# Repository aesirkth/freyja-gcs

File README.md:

freyja ground control station. talks with launchpad controller surtr over lora through brage and to fjaelar over brage.

## goals
- pcb should be able to run standalone from raspberry in case of raspberry malfunction
- every part from lcsc so that pcb can be assembled by jlcpcb. only select parts that have lot in stock. 
- 4-layer pcb. mainly for usb signal integrity

## tools
kicad + the plugin [impartGUI](https://github.com/Steffen-W/Import-LIB-KiCad-Plugin). impartGUI makes it really easy to get symbols and footprints downloaded directly from lcsc.

## TODO PCB
- [x] ESD/TVS diodes on every connecter and button
- Layout
- [x] configure stackup according to jlcpcb specs
- [x] usb 90 ohm diff-z
- [x] valve toggle switches
- [x] arm keyrings
- [x] 7-segment for redundancy operation without rpi
- leds:
  - [x] armed
  - [x] led for every valve toggle. should only be activated if surtr confirms position. blink if state is unknown
  - [x] connection status with surtr
  - [x] connection status with fjaelar
  - [x] fault
- [x] battery charging circuit
  - [x] undervoltage lockout
- [x] raspberry pi power
- [x] 2 can ports
  - [x] one for brage 
  - [x] one for connecting directly to launchpad
- [x] short circuit protection
- [x] fan connector
- [x] battery ntc work up to 70deg
- [x] led backlight driver
- [x] correct mounting holes
  - [x] dnp on resistors
- [ ] export 3d model and place raspberry to check fitment
- [x] silkscreen
  - [X] designators
  - [x] pinout
  - [x] name
  - [x] aesir
  - [x] connection
  - [x] battery polarity

## Components selection 
- 2 LiPo cells in series. (7.2V = 3.7 + 3.7V)
- Use DC-DC buck to step down the voltage to power RPi (min 4A continious current).
- We have to find a charging circuit for the 7.2V battries.
- Flip the toggle switch and hit send button to send command to sutur (this has to be done in the software).
- Therefore we will have 7 switches (6 toggle + 1 send)(in pull-up config).

### Part ID from LCSC
- C100042 - Capacitor
- C1788487 - Toggle switch
- C268254 - Push switch
- C965807 - Blue LED
- C965804 - Green LED
- C965799 - Red LED
- C95299 - Buzzer
- C42435361 - push button
- C18221474 - DC-DC booster
- C98220 - 10k ohm resistor

## To order
- [ ] 10-pin jst ph
- [ ] pcb

## SOFTWARE

We need two code bases. One Zephyr application that runs on the GCS PCB (PCB APP). And one Javascript and React + Python Raspberry Pi app (RPI APP) for displaying and managing the telemetry data. 

### PCB APP

Specs:
- Zephyr
- Talks with rocket and pad control through brage over CAN FD
- USB CDC to send data to RPI. Choose appropriate serialization format. 
- Sends valve toggle position only when send button has been pressed. 
- Shows status of valve on led.  

### RPI APP

Specs:
- Data to show:
  - Analog
    - With plot:
      - Altitude
      - Thrust. From loadcell. 
      - Orientation (from IMU)
      - Airbrake percantage
    - Without plot (only value):
      - Speed
      - Battery voltage
      - Countdown
      - Tank temperature. 6 ones spread over the tank.
      - Injector temperature
      - Post-combustion chamber temperature. 2 ones. 
      - Nozzle temperature. 2 ones.
      - Pressure at injector. 3 ones. 
    - Misc.
      - (GPS map if time over)
  - Discrete/bool:
    - Valve status (closed/open/unknown). 5 or 6 valves. 
    - Disarmed/armed
    - Ready/launched
    - Connection status with launch pad Surtr (down/up)
    - Connection status with rocket Fjalar (down/up)
    - Tank full float switch. (full/not full)
    - Main valve actuator (closed/open/unknown)
    - Abort valve actuator (closed/open/unknown)
    - CO2 activated [yes/no]
    - Parachute line cutters. 2 ones.
    - umbilical disconnect
    - tank bleed valve
- Gets binary data stream from GCS PCB. Hugo will help with protocol
  pack/unpack. [See wiki comparison of serialization formats](https://en.wikipedia.org/wiki/Comparison_of_data-serialization_formats). Maybe choose Protobuf or similar?
- Database to store all data

## venv
to activate python venv. have uv installed and execute
```
uv venv --system-site-packages
uv pip install -r pyproject.toml
```

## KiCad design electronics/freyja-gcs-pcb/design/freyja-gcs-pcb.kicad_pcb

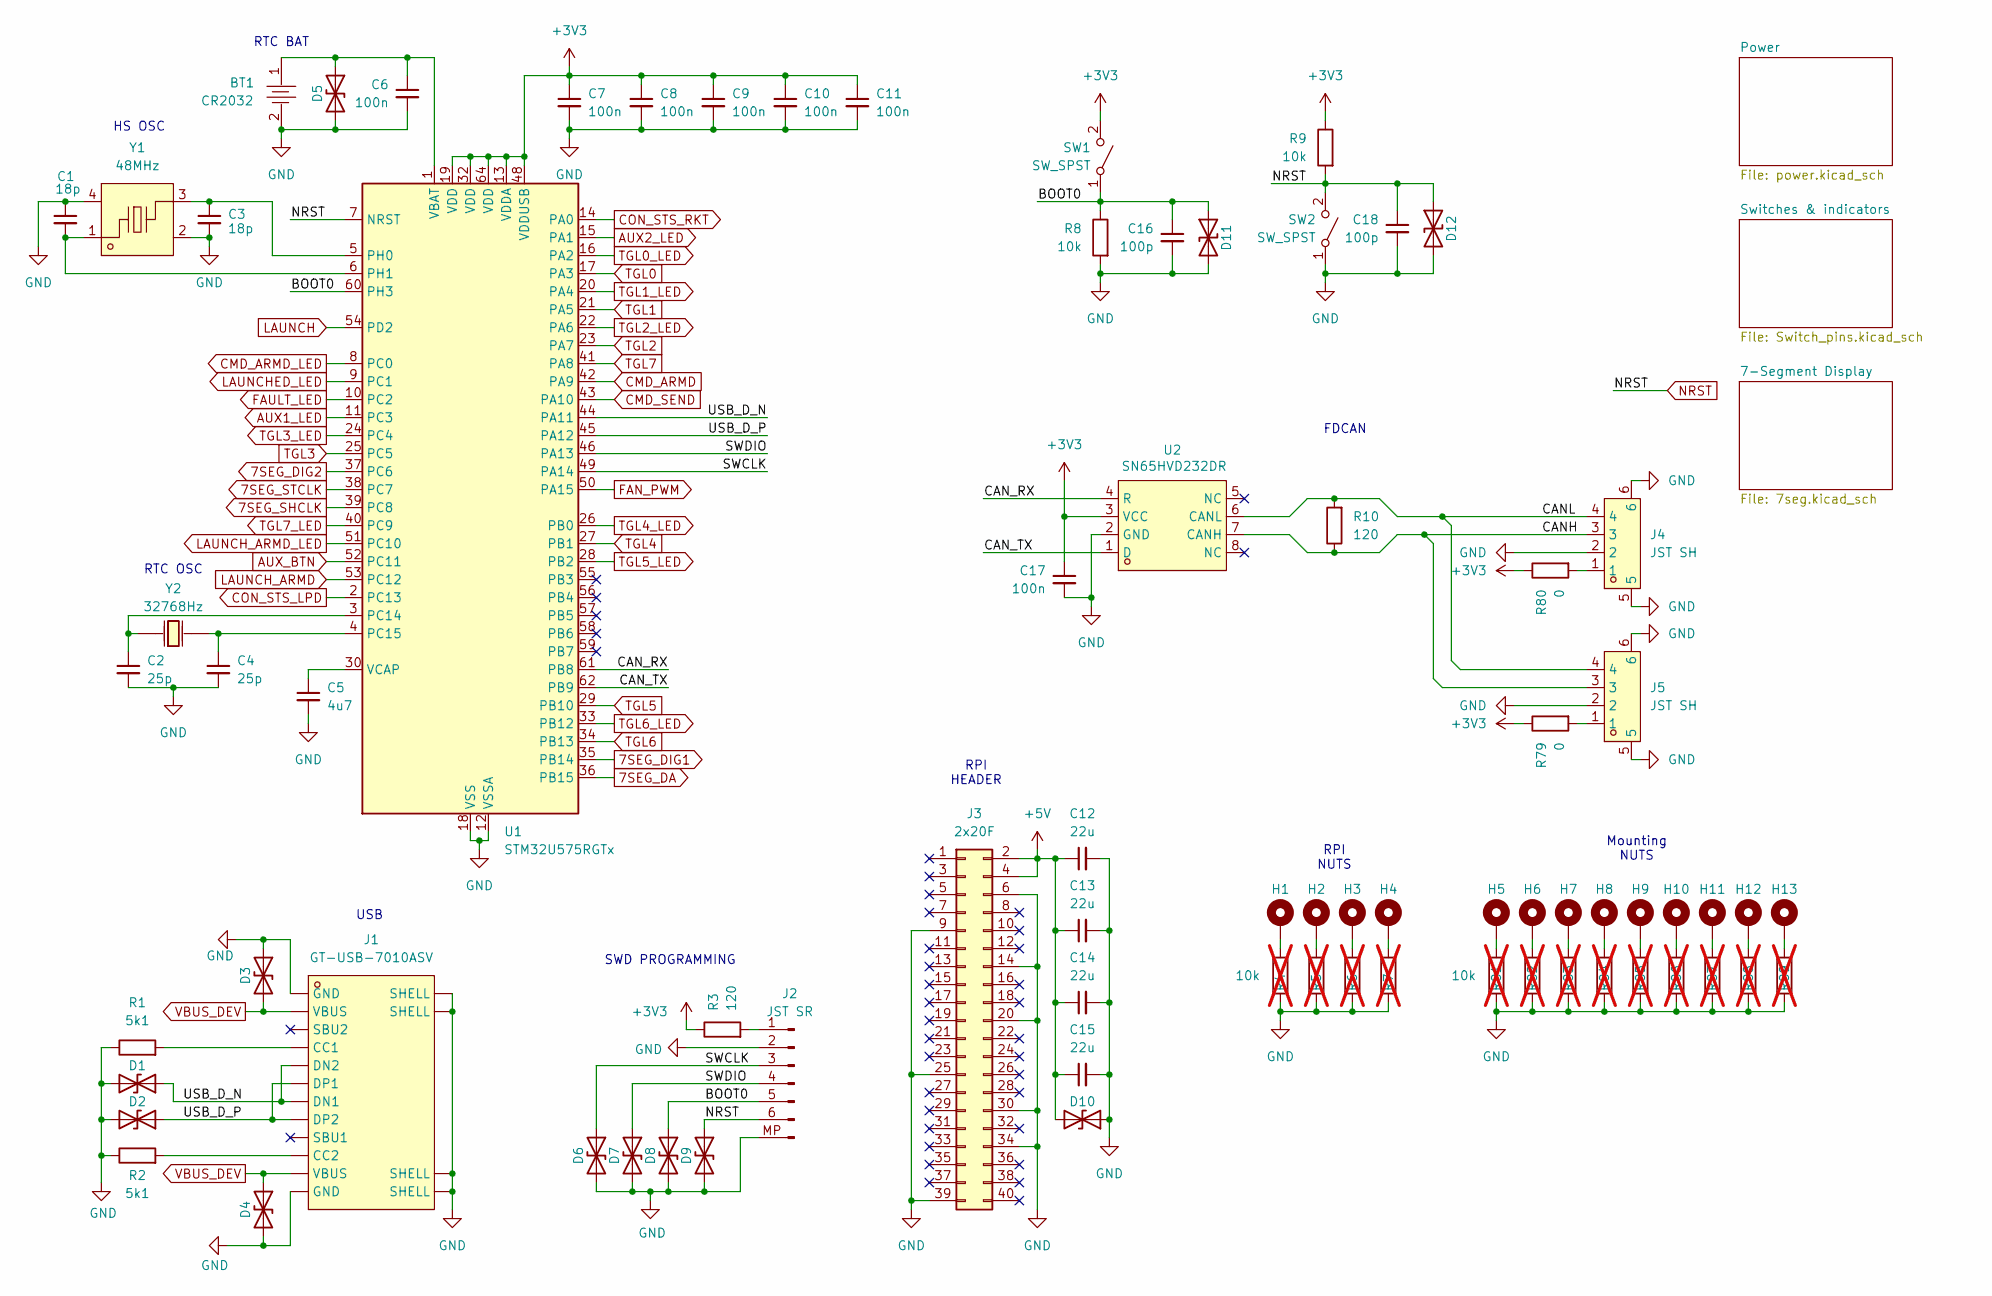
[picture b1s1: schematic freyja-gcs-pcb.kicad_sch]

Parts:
BT1: CR2032; BAT-TH_BS-2-1; LCSC Part C70376
C1, C3: 18p; C_0603_1608Metric; LCSC Part C5137620
C2, C4: 25p; C_0603_1608Metric; LCSC Part C282067
C5: 4u7; C_0603_1608Metric; LCSC Part C19666
C6, C7, C8, C9, C10, C11, C17: 100n; C_0603_1608Metric; LCSC Part C2762593
C12, C13, C14, C15: 22u; C1210; LCSC Part C100086
C16, C18: 100p; C_0603_1608Metric; LCSC Part C14665
D1, D2, D3, D4, D5, D6, D7, D8, D9, D10, D11, D12: 0603ESDA-05N; D_0603_1608Metric_Pad1.05x0.95mm_HandSolder; LCSC Part C316054
H1, H2, H3, H4: M2.5 12mm; SMTSO25120; LCSC Part C30182754
H5, H6, H7, H8, H9, H10, H11, H12, H13: M2.5 12mm; SMTSO25100; LCSC Part C2916330
J1: GT-USB-7010ASV; USB-C-SMD_G-SWITCH_GT-USB-7010ASV; LCSC Part C2988369
J2: JST SR; JST_SH_SM06B-SRSS-TB_1x06-1MP_P1.00mm_Horizontal; LCSC Part C2764185
J3: 2x20F; PinSocket_2x20_P2.54mm_Vertical; LCSC Part C2977589
J4, J5: JST SH; CONN-SMD_AFC10-S04QCA-00; LCSC Part C2764183
R1, R2: 5k1; R_0603_1608Metric; LCSC Part C23186
R3, R10: 120; R_0603_1608Metric; LCSC Part C22787
R4, R5, R6, R7, R81, R82, R83, R84, R85, R86, R87, R88, R89: 10k; R_0603_1608Metric; LCSC Part C98220; not fitted
R8, R9: 10k; R_0603_1608Metric; LCSC Part C98220
R79, R80: 0; R_0603_1608Metric; LCSC Part C2906974
SW1, SW2: SW_SPST; SW_SPST_PTS647_Sx38; LCSC Part C2689502
U1: STM32U575RGTx; LQFP-64_10x10mm_P0.5mm; LCSC Part C5270980
U2: SN65HVD232DR; SOIC-8_L5.0-W4.0-P1.27-LS6.0-BL; LCSC Part C30530
Y1: 48MHz; CRYSTAL-SMD_4P-L2.0-W1.6-BL_HUAXIN_CN4; LCSC Part C2933019
Y2: 32768Hz; OSC-TH_BD1.9-P0.70; LCSC Part C403947

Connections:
7SEG_DA: U1.36 (PB15); also elsewhere on the board
7SEG_DIG1: U1.35 (PB14); also elsewhere on the board
7SEG_DIG2: U1.37 (PC6); also elsewhere on the board
7SEG_SHCLK: U1.39 (PC8); also elsewhere on the board
7SEG_STCLK: U1.38 (PC7); also elsewhere on the board
+3V3: C7.1, C8.1, C9.1, C10.1, C11.1, C17.1, R3.1, R9.1, R79.1, R80.1, SW1.2 (B), U1.13 (VDDA), U1.19 (VDD), U1.32 (VDD), U1.48 (VDDUSB), U1.64 (VDD), U2.3 (VCC); also elsewhere on the board
+5V: C12.1, C13.1, C14.1, C15.1, D10.2 (A2), J3.2, J3.4; also elsewhere on the board
/BOOT0: C16.1, D8.1 (A1), D11.1 (A1), J2.5, R8.1, SW1.1 (A), U1.60 (PH3)
/CANH: J4.3, J5.3, R10.1, U2.7 (CANH)
/CANL: J4.4, J5.4, R10.2, U2.6 (CANL)
/CAN_RX: U1.61 (PB8), U2.4 (R)
/CAN_TX: U1.62 (PB9), U2.1 (D)
/SWCLK: D6.1 (A1), J2.3, U1.49 (PA14)
/SWDIO: D7.1 (A1), J2.4, U1.46 (PA13)
/USB_D_N: D1.1 (A1), J1.A7 (DN1), J1.B7 (DN2), U1.44 (PA11)
/USB_D_P: D2.1 (A1), J1.A6 (DP1), J1.B6 (DP2), U1.45 (PA12)
AUX1_LED: U1.11 (PC3); also elsewhere on the board
AUX2_LED: U1.15 (PA1); also elsewhere on the board
AUX_BTN: U1.52 (PC11); also elsewhere on the board
CMD_ARMD: U1.42 (PA9); also elsewhere on the board
CMD_ARMD_LED: U1.8 (PC0); also elsewhere on the board
CMD_SEND: U1.43 (PA10); also elsewhere on the board
CON_STS_LPD: U1.2 (PC13); also elsewhere on the board
CON_STS_RKT: U1.14 (PA0); also elsewhere on the board
FAN_PWM: U1.50 (PA15); also elsewhere on the board
FAULT_LED: U1.10 (PC2); also elsewhere on the board
GND: BT1.2, C1.1, C2.2, C3.2, C4.2, C5.2, C6.2, C7.2, C8.2, C9.2, C10.2, C11.2, C12.2, C13.2, C14.2, C15.2, C16.2, C17.2, C18.2, D1.2 (A2), D2.2 (A2), D3.1 (A1), D4.2 (A2), D5.2 (A2), D6.2 (A2), D7.2 (A2), D8.2 (A2), D9.2 (A2), D10.1 (A1), D11.2 (A2), D12.2 (A2), J1.1 (SHELL), J1.2 (SHELL), J1.3 (SHELL), J1.4 (SHELL), J1.A1B12 (GND), J1.B1A12 (GND), J2.2, J2.MP, J3.6, J3.9, J3.14, J3.20, J3.25, J3.30, J3.34, J3.39, J4.2, J4.5, J4.6, J5.2, J5.5, J5.6, R1.1, R2.1, R4.2, R5.2, R6.2, R7.2, R8.2, R81.2, R82.2, R83.2, R84.2, R85.2, R86.2, R87.2, R88.2, R89.2, SW2.1 (A), U1.12 (VSSA), U1.18 (VSS), U1.31 (VSS), U1.47 (VSS), U1.63 (VSS), U2.2 (GND), Y1.2 (GND), Y1.4 (GND); also elsewhere on the board
LAUNCH: U1.54 (PD2); also elsewhere on the board
LAUNCHED_LED: U1.9 (PC1); also elsewhere on the board
LAUNCH_ARMD: U1.53 (PC12); also elsewhere on the board
LAUNCH_ARMD_LED: U1.51 (PC10); also elsewhere on the board
NRST: C18.1, D9.1 (A1), D12.1 (A1), J2.6, R9.2, SW2.2 (B), U1.7 (NRST); also elsewhere on the board
unnamed: BT1.1, C6.1, D5.1 (A1), U1.1 (VBAT)
unnamed: H1.1, R4.1
unnamed: H2.1, R5.1
unnamed: H3.1, R6.1
unnamed: H4.1, R7.1
unnamed: H5.1, R81.1
unnamed: H6.1, R82.1
unnamed: H7.1, R83.1
unnamed: H8.1, R84.1
unnamed: H9.1, R85.1
unnamed: H10.1, R86.1
unnamed: H11.1, R87.1
unnamed: H12.1, R88.1
unnamed: H13.1, R89.1
unnamed: J1.A5 (CC1), R1.2
unnamed: J1.B5 (CC2), R2.2
unnamed: J2.1, R3.2
unnamed: J4.1, R80.2
unnamed: J5.1, R79.2
unnamed: C2.1, U1.3 (PC14), Y2.1 (OSC1)
unnamed: C4.1, U1.4 (PC15), Y2.2 (OSC2)
unnamed: C3.1, U1.5 (PH0), Y1.3
unnamed: C1.2, U1.6 (PH1), Y1.1
unnamed: C5.1, U1.30 (VCAP)
TGL0: U1.17 (PA3); also elsewhere on the board
TGL0_LED: U1.16 (PA2); also elsewhere on the board
TGL1: U1.21 (PA5); also elsewhere on the board
TGL1_LED: U1.20 (PA4); also elsewhere on the board
TGL2: U1.23 (PA7); also elsewhere on the board
TGL2_LED: U1.22 (PA6); also elsewhere on the board
TGL3: U1.25 (PC5); also elsewhere on the board
TGL3_LED: U1.24 (PC4); also elsewhere on the board
TGL4: U1.27 (PB1); also elsewhere on the board
TGL4_LED: U1.26 (PB0); also elsewhere on the board
TGL5: U1.29 (PB10); also elsewhere on the board
TGL5_LED: U1.28 (PB2); also elsewhere on the board
TGL6: U1.34 (PB13); also elsewhere on the board
TGL6_LED: U1.33 (PB12); also elsewhere on the board
TGL7: U1.41 (PA8); also elsewhere on the board
TGL7_LED: U1.40 (PC9); also elsewhere on the board
VBUS_DEV: D3.2 (A2), D4.1 (A1), J1.A4B9 (VBUS), J1.B4A9 (VBUS); also elsewhere on the board

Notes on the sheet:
HS OSC
FDCAN
RTC BAT
SWD PROGRAMMING
RPI HEADER
RTC OSC
Mounting NUTS
RPI NUTS
USB

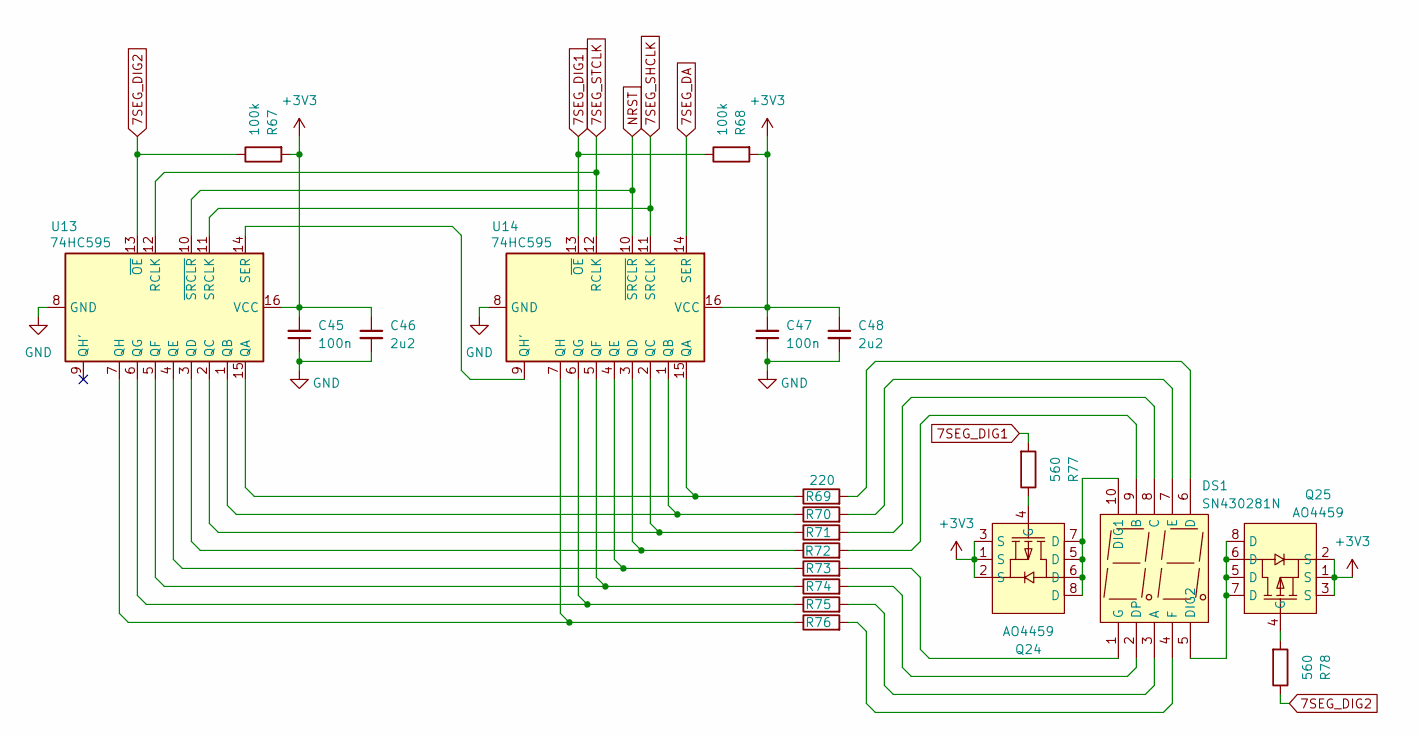
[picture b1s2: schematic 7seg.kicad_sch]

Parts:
C45, C47: 100n; C_0603_1608Metric; LCSC Part C2762593
C46, C48: 2u2; C_0603_1608Metric; LCSC Part C913904
DS1: SN430281N; LED-SEG-TH_10P-L15.0-W10.0-P2.54-S7.40-BL; LCSC Part C182258
Q24, Q25: AO4459; SOP-8_L5.0-W4.0-P1.27-LS6.2-BL; LCSC Part C49047
R67, R68: 100k; R_0603_1608Metric; LCSC Part C25803
R69, R70, R71, R72, R73, R74, R75, R76: 220; R_0603_1608Metric; LCSC Part C22962
R77, R78: 560; R_0603_1608Metric; LCSC Part C23204
U13, U14: 74HC595; SOIC-16_L9.9-W3.9-P1.27-LS6.0-BL; LCSC Part C5947

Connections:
7SEG_DA: U14.14 (SER); also elsewhere on the board
7SEG_DIG1: R68.1, R77.2, U14.13 (~OE); also elsewhere on the board
7SEG_DIG2: R67.1, R78.1, U13.13 (~OE); also elsewhere on the board
7SEG_SHCLK: U13.11 (SRCLK), U14.11 (SRCLK); also elsewhere on the board
7SEG_STCLK: U13.12 (RCLK), U14.12 (RCLK); also elsewhere on the board
+3V3: C45.2, C46.1, C47.2, C48.1, Q24.1 (S), Q24.2 (S), Q24.3 (S), Q25.1 (S), Q25.2 (S), Q25.3 (S), R67.2, R68.2, U13.16 (VCC), U14.16 (VCC); also elsewhere on the board
GND: C45.1, C46.2, C47.1, C48.2, U13.8 (GND), U14.8 (GND); also elsewhere on the board
NRST: U13.10 (~SRCLR), U14.10 (~SRCLR); also elsewhere on the board
unnamed: DS1.3 (A), R75.2
unnamed: DS1.9 (B), R72.2
unnamed: DS1.8 (C), R71.2
unnamed: DS1.6 (D), R69.2
unnamed: DS1.10 (DIG1), Q24.5 (D), Q24.6 (D), Q24.7 (D), Q24.8 (D)
unnamed: DS1.5 (DIG2), Q25.5 (D), Q25.6 (D), Q25.7 (D), Q25.8 (D)
unnamed: DS1.2 (DP), R74.2
unnamed: DS1.7 (E), R70.2
unnamed: DS1.4 (F), R76.2
unnamed: DS1.1 (G), R73.2
unnamed: Q24.4 (G), R77.1
unnamed: Q25.4 (G), R78.2
unnamed: R69.1, U13.15 (QA), U14.15 (QA)
unnamed: R70.1, U13.1 (QB), U14.1 (QB)
unnamed: R71.1, U13.2 (QC), U14.2 (QC)
unnamed: R72.1, U13.3 (QD), U14.3 (QD)
unnamed: R73.1, U13.4 (QE), U14.4 (QE)
unnamed: R74.1, U13.5 (QF), U14.5 (QF)
unnamed: R75.1, U13.6 (QG), U14.6 (QG)
unnamed: R76.1, U13.7 (QH), U14.7 (QH)
unnamed: U13.14 (SER), U14.9 (QH')

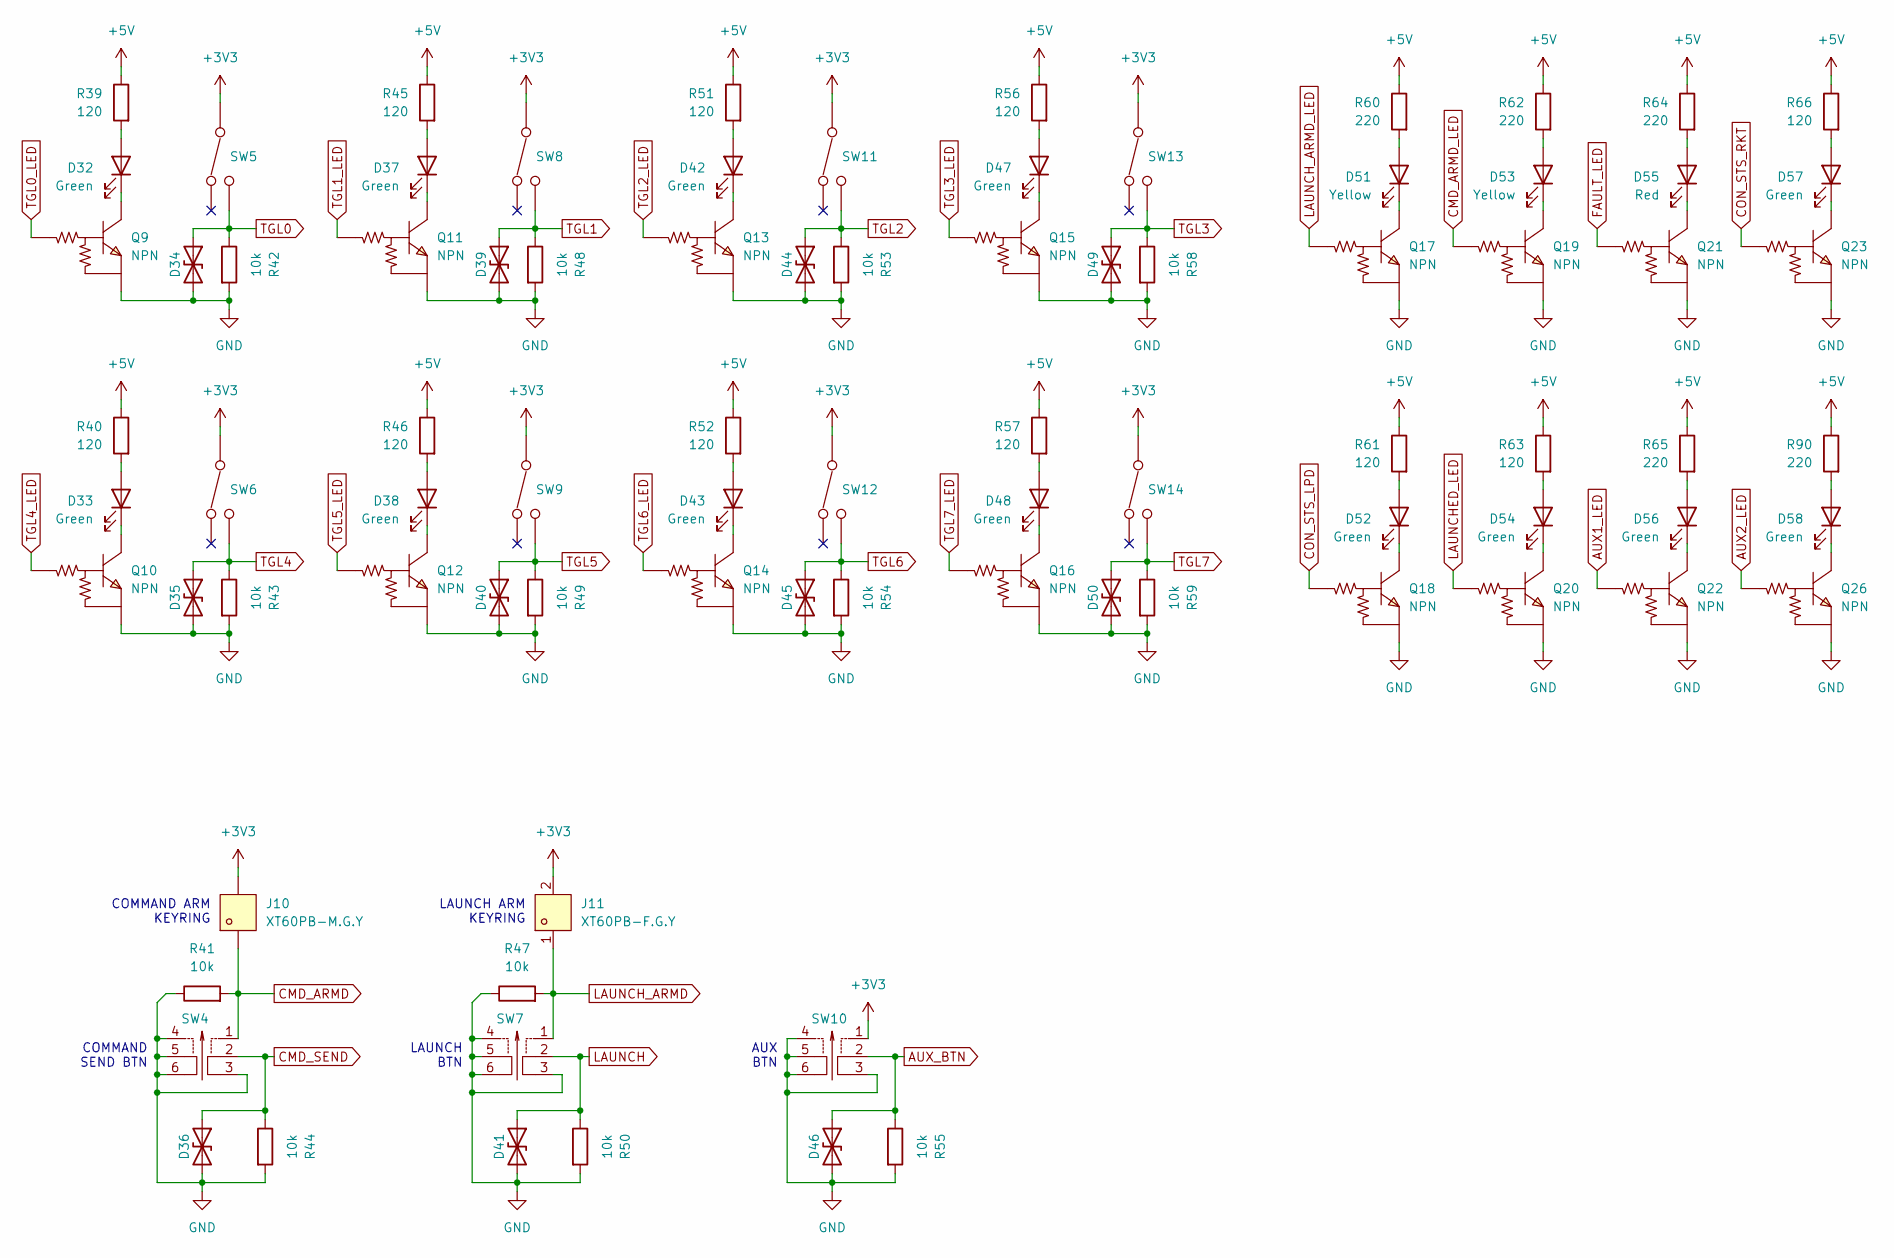
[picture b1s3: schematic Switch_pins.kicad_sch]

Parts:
D32, D33, D37, D38, D42, D43, D47, D48, D52, D54, D56, D57, D58: Green; LED-TH_BD5.9-P2.54-RD_GREEN; LCSC Part C2895548
D34, D35, D36, D39, D40, D41, D44, D45, D46, D49, D50: 0603ESDA-05N; D_0603_1608Metric_Pad1.05x0.95mm_HandSolder; LCSC Part C316054
D51, D53: Yellow; LED-TH_BD5.9-P2.54-RD_GREEN; LCSC Part C2895494
D55: Red; LED-TH_BD5.9-P2.54-RD_GREEN; LCSC Part C2895492
J10: XT60PB-M.G.Y; CONN-TH_XT60PB-M; LCSC Part C19268037
J11: XT60PB-F.G.Y; CONN-TH_XT60PB-F.G.Y; LCSC Part C19268038
Q9, Q10, Q11, Q12, Q13, Q14, Q15, Q16, Q17, Q18, Q19, Q20, Q21, Q22, Q23, Q26: NPN; SOT-416_L1.6-W0.8-P1.00-LS1.6-BR; LCSC Part C96459
R39, R40, R45, R46, R51, R52, R56, R57, R61, R63, R66: 120; R_0603_1608Metric; LCSC Part C22787
R41, R42, R43, R44, R47, R48, R49, R50, R53, R54, R55, R58, R59: 10k; R_0603_1608Metric; LCSC Part C98220
R60, R62, R64, R65, R90: 220; R_0603_1608Metric; LCSC Part C22962
SW4, SW7, SW10: PB22E09071; SW-TH_6P-L8.5-W8.5-P2.54-LS5.5; LCSC Part C194405
SW5, SW6, SW8, SW9, SW11, SW12, SW13, SW14: 2MS1T1B1M2QES; SW-TH_2MS1T1B1M2QES-5; LCSC Part C908280

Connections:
+3V3: J10.2, J11.2, SW5.2, SW6.2, SW8.2, SW9.2, SW10.1, SW11.2, SW12.2, SW13.2, SW14.2; also elsewhere on the board
+5V: R39.1, R40.1, R45.1, R46.1, R51.1, R52.1, R56.1, R57.1, R60.1, R61.1, R62.1, R63.1, R64.1, R65.1, R66.1, R90.1; also elsewhere on the board
AUX1_LED: Q22.1 (B); also elsewhere on the board
AUX2_LED: Q26.1 (B); also elsewhere on the board
AUX_BTN: D46.1 (A1), R55.1, SW10.2; also elsewhere on the board
CMD_ARMD: J10.1, R41.2, SW4.1; also elsewhere on the board
CMD_ARMD_LED: Q19.1 (B); also elsewhere on the board
CMD_SEND: D36.1 (A1), R44.1, SW4.2; also elsewhere on the board
CON_STS_LPD: Q18.1 (B); also elsewhere on the board
CON_STS_RKT: Q23.1 (B); also elsewhere on the board
FAULT_LED: Q21.1 (B); also elsewhere on the board
GND: D34.2 (A2), D35.2 (A2), D36.2 (A2), D39.2 (A2), D40.2 (A2), D41.2 (A2), D44.2 (A2), D45.2 (A2), D46.2 (A2), D49.2 (A2), D50.2 (A2), Q9.2 (E), Q10.2 (E), Q11.2 (E), Q12.2 (E), Q13.2 (E), Q14.2 (E), Q15.2 (E), Q16.2 (E), Q17.2 (E), Q18.2 (E), Q19.2 (E), Q20.2 (E), Q21.2 (E), Q22.2 (E), Q23.2 (E), Q26.2 (E), R41.1, R42.2, R43.2, R44.2, R47.1, R48.2, R49.2, R50.2, R53.2, R54.2, R55.2, R58.2, R59.2, SW4.3, SW4.4, SW4.5, SW4.6, SW7.3, SW7.4, SW7.5, SW7.6, SW10.3, SW10.4, SW10.5, SW10.6; also elsewhere on the board
LAUNCH: D41.1 (A1), R50.1, SW7.2; also elsewhere on the board
LAUNCHED_LED: Q20.1 (B); also elsewhere on the board
LAUNCH_ARMD: J11.1, R47.2, SW7.1; also elsewhere on the board
LAUNCH_ARMD_LED: Q17.1 (B); also elsewhere on the board
unnamed: D32.2 (A), R39.2
unnamed: D32.1 (K), Q9.3 (C)
unnamed: D33.2 (A), R40.2
unnamed: D33.1 (K), Q10.3 (C)
unnamed: D37.2 (A), R45.2
unnamed: D37.1 (K), Q11.3 (C)
unnamed: D38.2 (A), R46.2
unnamed: D38.1 (K), Q12.3 (C)
unnamed: D42.2 (A), R51.2
unnamed: D42.1 (K), Q13.3 (C)
unnamed: D43.2 (A), R52.2
unnamed: D43.1 (K), Q14.3 (C)
unnamed: D47.2 (A), R56.2
unnamed: D47.1 (K), Q15.3 (C)
unnamed: D48.2 (A), R57.2
unnamed: D48.1 (K), Q16.3 (C)
unnamed: D51.2 (A), R60.2
unnamed: D51.1 (K), Q17.3 (C)
unnamed: D52.2 (A), R61.2
unnamed: D52.1 (K), Q18.3 (C)
unnamed: D53.2 (A), R62.2
unnamed: D53.1 (K), Q19.3 (C)
unnamed: D54.2 (A), R63.2
unnamed: D54.1 (K), Q20.3 (C)
unnamed: D55.2 (A), R64.2
unnamed: D55.1 (K), Q21.3 (C)
unnamed: D56.2 (A), R65.2
unnamed: D56.1 (K), Q22.3 (C)
unnamed: D57.2 (A), R66.2
unnamed: D57.1 (K), Q23.3 (C)
unnamed: D58.2 (A), R90.2
unnamed: D58.1 (K), Q26.3 (C)
TGL0: D34.1 (A1), R42.1, SW5.3; also elsewhere on the board
TGL0_LED: Q9.1 (B); also elsewhere on the board
TGL1: D39.1 (A1), R48.1, SW8.3; also elsewhere on the board
TGL1_LED: Q11.1 (B); also elsewhere on the board
TGL2: D44.1 (A1), R53.1, SW11.3; also elsewhere on the board
TGL2_LED: Q13.1 (B); also elsewhere on the board
TGL3: D49.1 (A1), R58.1, SW13.3; also elsewhere on the board
TGL3_LED: Q15.1 (B); also elsewhere on the board
TGL4: D35.1 (A1), R43.1, SW6.3; also elsewhere on the board
TGL4_LED: Q10.1 (B); also elsewhere on the board
TGL5: D40.1 (A1), R49.1, SW9.3; also elsewhere on the board
TGL5_LED: Q12.1 (B); also elsewhere on the board
TGL6: D45.1 (A1), R54.1, SW12.3; also elsewhere on the board
TGL6_LED: Q14.1 (B); also elsewhere on the board
TGL7: D50.1 (A1), R59.1, SW14.3; also elsewhere on the board
TGL7_LED: Q16.1 (B); also elsewhere on the board

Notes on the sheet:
LAUNCH BTN
AUX BTN
COMMAND ARM KEYRING
COMMAND SEND BTN
LAUNCH ARM KEYRING

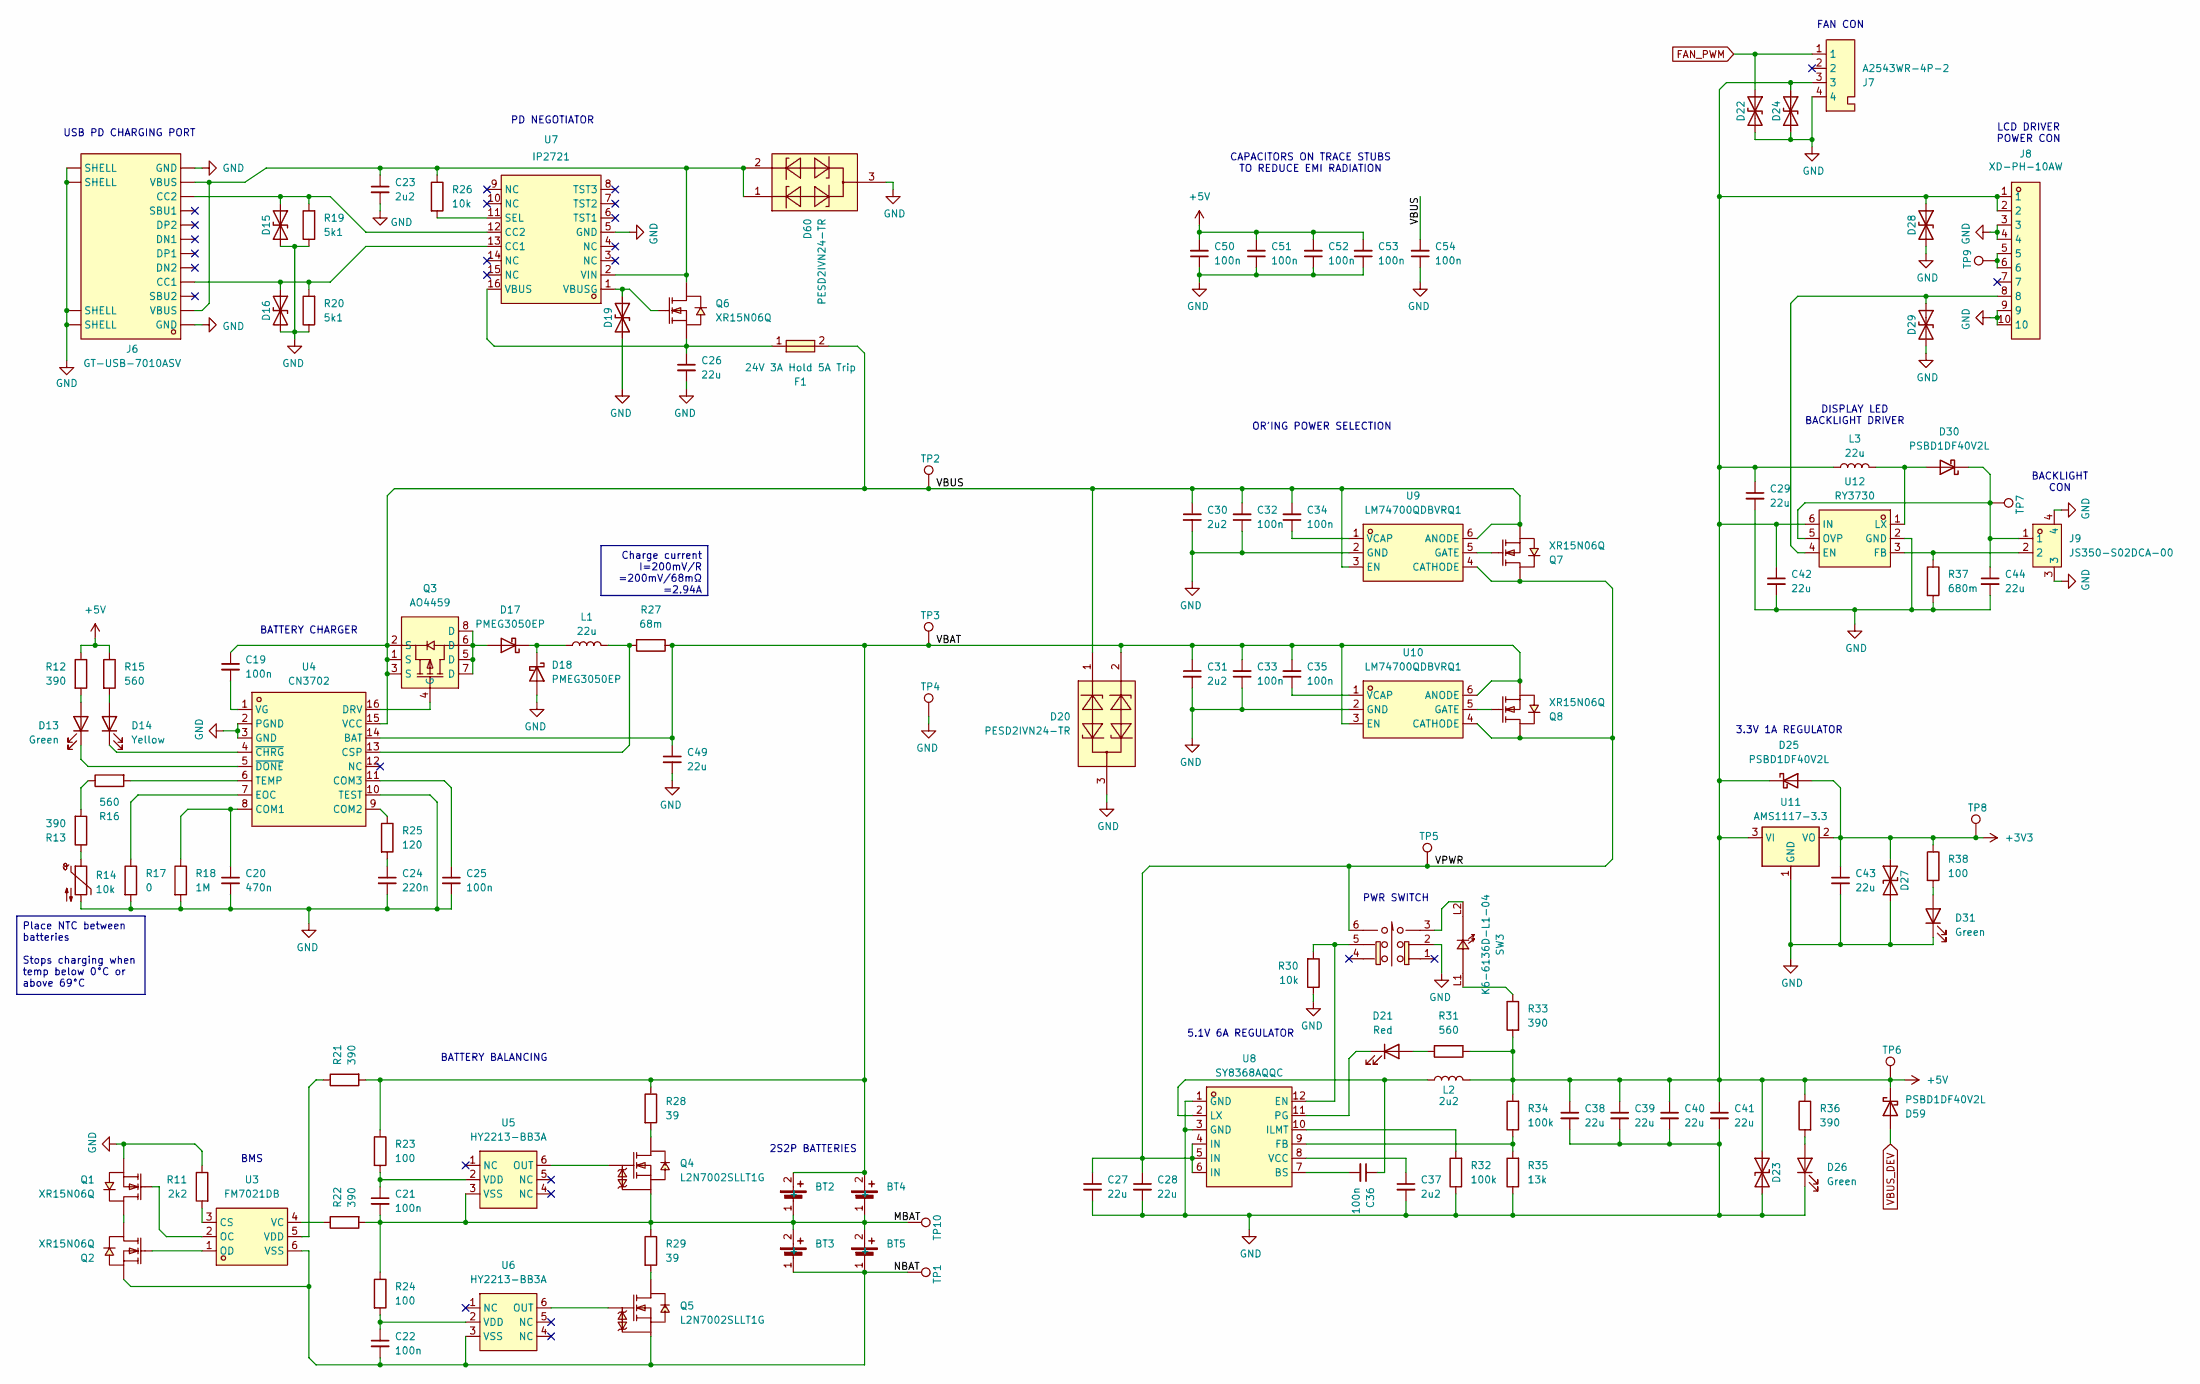
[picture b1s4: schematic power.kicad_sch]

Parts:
BT2, BT3, BT4, BT5: BH-18650-B1BA002; BATTERY-SMD_18650-1S-L77.1-W20.7-1; LCSC Part C2988620
C19, C21, C22, C25, C32, C33, C34, C35, C36, C50, C51, C52, C53, C54: 100n; C_0603_1608Metric; LCSC Part C2762593
C20: 470n; C_0603_1608Metric; LCSC Part C513577
C23, C30, C31, C37: 2u2; C_0603_1608Metric; LCSC Part C913904
C24: 220n; C_0603_1608Metric; LCSC Part C344195
C26, C27, C28, C44, C49: 22u; C2220; LCSC Part C784103
C29, C38, C39, C40, C41, C42, C43: 22u; C1210; LCSC Part C100086
D13: Green; LED-TH_BD5.9-P2.54-RD_GREEN; LCSC Part C2895548
D14: Yellow; LED-TH_BD5.9-P2.54-RD_GREEN; LCSC Part C2895494
D15, D16, D19, D22, D23, D24, D27, D28, D29: 0603ESDA-05N; D_0603_1608Metric_Pad1.05x0.95mm_HandSolder; LCSC Part C316054
D17, D18: PMEG3050EP; SOD-128_L3.7-W2.5-LS4.7-RD; LCSC Part C50603
D20, D60: PESD2IVN24-TR; TO-236AB_L2.9-W1.3-P0.95-LS2.3-BR; LCSC Part C406047
D21: Red; LED0603-RD_RED; LCSC Part C965799
D25, D30, D59: PSBD1DF40V2L; SOD-123FL_L2.8-W1.8-LS3.8-RD; LCSC Part C496544
D26, D31: Green; LED0603-RD_GREEN; LCSC Part C965804
F1: 24V 3A Hold 5A Trip; F1812; LCSC Part C20627123
J6: GT-USB-7010ASV; USB-C-SMD_G-SWITCH_GT-USB-7010ASV; LCSC Part C2988369
J7: A2543WR-4P-2; CONN-TH_PHD2-4P-2.54; LCSC Part C239371
J8: XD-PH-10AW; CONN-TH_10P-P2.00_HCTL_PH-10AW; LCSC Part C2908642
J9: JS350-S02DCA-00; CONN-SMD_JS350-S02DCA-00; LCSC Part C7529566
L1, L3: 22u; IND-SMD_FCH1350-220M; LCSC Part C22367869
L2: 2u2; IND-SMD_L13.5-W12.6; LCSC Part C408512
Q1, Q2, Q6, Q7, Q8: XR15N06Q; SOT-89-3_L4.5-W2.5-P1.50-LS4.2-BR; LCSC Part C7422896
Q3: AO4459; SOP-8_L5.0-W4.0-P1.27-LS6.2-BL; LCSC Part C49047
Q4, Q5: L2N7002SLLT1G; SOT-23-3_L3.0-W1.7-P0.95-LS2.9-BR; LCSC Part C22446827
R11: 2k2; R_0603_1608Metric; LCSC Part C4190
R12, R13, R21, R22, R33, R36: 390; R_0603_1608Metric; LCSC Part C23151
R14, R26, R30: 10k; R_0603_1608Metric; LCSC Part C98220
R15, R16, R31: 560; R_0603_1608Metric; LCSC Part C23204
R17: 0; R_0603_1608Metric; LCSC Part C2906974
R18: 1M; R_0603_1608Metric; LCSC Part C22935
R19, R20: 5k1; R_0603_1608Metric; LCSC Part C23186
R23, R24, R38: 100; R_0603_1608Metric; LCSC Part C22775
R25: 120; R_0603_1608Metric; LCSC Part C22787
R27: 68m; R_2512_6332Metric_Pad1.40x3.35mm_HandSolder; LCSC Part C419718
R28, R29: 39; R_0603_1608Metric; LCSC Part C2907032
R32, R34: 100k; R_0603_1608Metric; LCSC Part C25803
R35: 13k; R_0603_1608Metric; LCSC Part C2906992
R37: 680m; R_1206_3216Metric; LCSC Part C620833
SW3: K6-6136D-L1-04; SW-TH_K6-6136D-L1-04; LCSC Part C128976
TP1, TP2, TP3, TP4, TP5, TP6, TP7, TP8, TP9, TP10: TestPoint; TestPoint_Pad_D3.0mm
U3: FM7021DB; SOT-23-6_L2.9-W1.6-P0.95-LS2.8-BR; LCSC Part C7420386
U4: CN3702; TSSOP-16_L5.0-W4.4-P0.65-LS6.4-BL; LCSC Part C40655
U5, U6: HY2213-BB3A; SOT-23-6_L2.9-W1.6-P0.95-LS2.8-BR; LCSC Part C113632
U7: IP2721; TSSOP-16_L5.0-W4.4-P0.65-LS6.4-BL; LCSC Part C603176
U8: SY8368AQQC; QFN-12_L3.0-W3.0-P0.45-TL-EP; LCSC Part C207642
U9, U10: LM74700QDBVRQ1; SOT-23-6_L2.9-W1.6-P0.95-LS2.8-BL; LCSC Part C2941042
U11: AMS1117-3.3; SOT-223-3_TabPin2; LCSC Part C6186
U12: RY3730; SOT-23-6_L2.9-W1.6-P0.95-LS2.8-BL; LCSC Part C370887

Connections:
+3V3: C43.1, D25.2 (A), D27.1 (A1), R38.1, TP8.1, U11.2 (VO); also elsewhere on the board
+5V: C29.1, C38.1, C39.1, C40.1, C41.1, C42.1, C50.2, C51.2, C52.2, C53.2, D23.1 (A1), D24.1 (A1), D25.1 (K), D28.1 (A1), D59.1 (K), J7.3, J8.1, J8.2, L2.2, L3.2, R12.1, R15.1, R31.1, R33.2, R34.2, R36.1, TP6.1, U11.3 (VI), U12.6 (IN); also elsewhere on the board
/Power/MBAT: BT2.1 (-), BT3.2 (+), BT4.1 (-), BT5.2 (+), C21.2, Q4.2 (S), R22.2, R24.1, R29.1, TP10.1, U5.3 (VSS)
/Power/NBAT: BT3.1 (-), BT5.1 (-), C22.2, Q2.3 (S), Q5.2 (S), TP1.1, U3.6 (VSS), U6.3 (VSS)
/Power/VBAT: BT2.2 (+), BT4.2 (+), C31.1, C33.2, C35.2, C49.1, D20.2, Q8.3 (S), R21.2, R23.1, R27.1, R28.1, TP3.1, U4.14 (BAT), U10.3 (EN), U10.6 (ANODE)
/Power/VBUS: C19.1, C30.1, C32.2, C34.2, C54.2, D20.1, F1.2, Q3.1 (S), Q3.2 (S), Q3.3 (S), Q7.3 (S), TP2.1, U4.15 (VCC), U9.3 (EN), U9.6 (ANODE)
/Power/VPWR: C27.1, C28.1, Q7.2 (D), Q8.2 (D), SW3.6, TP5.1, U8.4 (IN), U8.5 (IN), U8.6 (IN), U9.4 (CATHODE), U10.4 (CATHODE)
FAN_PWM: D22.1 (A1), J7.1; also elsewhere on the board
GND: C20.2, C23.2, C24.2, C25.2, C26.2, C27.2, C28.2, C29.2, C30.2, C31.2, C32.1, C33.1, C37.2, C38.2, C39.2, C40.2, C41.2, C42.2, C43.2, C44.2, C49.2, C50.1, C51.1, C52.1, C53.1, C54.1, D15.2 (A2), D16.2 (A2), D18.2 (A), D19.2 (A2), D20.3, D22.2 (A2), D23.2 (A2), D24.2 (A2), D26.1 (K), D27.2 (A2), D28.2 (A2), D29.2 (A2), D31.1 (K), D60.3, J6.1 (SHELL), J6.2 (SHELL), J6.3 (SHELL), J6.4 (SHELL), J6.A1B12 (GND), J6.B1A12 (GND), J7.4, J8.3, J8.4, J8.9, J8.10, J9.3, J9.4, Q1.3 (S), R11.1, R14.2, R17.2, R18.2, R19.1, R20.1, R30.1, R32.1, R35.1, R37.2, SW3.2, TP4.1, U4.2 (PGND), U4.3 (GND), U4.10 (TEST), U7.5 (GND), U8.1 (GND), U8.3 (GND), U9.2 (GND), U10.2 (GND), U11.1 (GND), U12.2 (GND); also elsewhere on the board
unnamed: C24.1, R25.2
unnamed: D13.2 (A), R12.2
unnamed: D13.1 (K), U4.5 (~DONE)
unnamed: D14.2 (A), R15.2
unnamed: D14.1 (K), U4.4 (~CHRG)
unnamed: D15.1 (A1), J6.B5 (CC2), R19.2, U7.12 (CC2)
unnamed: D16.1 (A1), J6.A5 (CC1), R20.2, U7.13 (CC1)
unnamed: D17.2 (A), Q3.5 (D), Q3.6 (D), Q3.7 (D), Q3.8 (D)
unnamed: D17.1 (K), D18.1 (K), L1.2
unnamed: D19.1 (A1), Q6.1 (G), U7.1 (VBUSG)
unnamed: D21.2 (A), R31.2
unnamed: D21.1 (K), U8.11 (PG)
unnamed: D26.2 (A), R36.2
unnamed: D29.1 (A1), J8.8, U12.4 (EN)
unnamed: D30.2 (A), L3.1, U12.1 (LX)
unnamed: C44.1, D30.1 (K), J9.1, TP7.1, U12.5 (OVP)
unnamed: D31.2 (A), R38.2
unnamed: J8.5, J8.6, TP9.1
unnamed: Q1.2 (D), Q2.2 (D)
unnamed: Q1.1 (G), U3.2 (OC)
unnamed: Q2.1 (G), U3.1 (OD)
unnamed: Q3.4 (G), U4.16 (DRV)
unnamed: Q4.3 (D), R28.2
unnamed: Q4.1 (G), U5.6 (OUT)
unnamed: Q5.3 (D), R29.2
unnamed: Q5.1 (G), U6.6 (OUT)
unnamed: C23.1, D60.1, D60.2, J6.A4B9 (VBUS), J6.B4A9 (VBUS), Q6.2 (D), R26.1, U7.2 (VIN)
unnamed: C26.1, F1.1, Q6.3 (S), U7.16 (VBUS)
unnamed: Q7.1 (G), U9.5 (GATE)
unnamed: Q8.1 (G), U10.5 (GATE)
unnamed: R13.1, R14.1
unnamed: R13.2, R16.1
unnamed: R33.1, SW3.L1 (+)
unnamed: SW3.3, SW3.L2 (-)
unnamed: R11.2, U3.3 (CS)
unnamed: R22.1, U3.4 (VC)
unnamed: R21.1, U3.5 (VDD)
unnamed: C20.1, R18.1, U4.8 (COM1)
unnamed: R25.1, U4.9 (COM2)
unnamed: C25.1, U4.11 (COM3)
unnamed: L1.1, R27.2, U4.13 (CSP)
unnamed: R17.1, U4.7 (EOC)
unnamed: R16.2, U4.6 (TEMP)
unnamed: C19.2, U4.1 (VG)
unnamed: C21.1, R23.2, U5.2 (VDD)
unnamed: C22.1, R24.2, U6.2 (VDD)
unnamed: R26.2, U7.11 (SEL)
unnamed: C36.2, U8.7 (BS)
unnamed: R30.2, SW3.5, U8.12 (EN)
unnamed: R34.1, R35.2, U8.9 (FB)
unnamed: R32.2, U8.10 (ILMT)
unnamed: C36.1, L2.1, U8.2 (LX)
unnamed: C37.1, U8.8 (VCC)
unnamed: C34.1, U9.1 (VCAP)
unnamed: C35.1, U10.1 (VCAP)
unnamed: J9.2, R37.1, U12.3 (FB)
VBUS_DEV: D59.2 (A); also elsewhere on the board

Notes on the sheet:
2S2P BATTERIES
DISPLAY LED BACKLIGHT DRIVER
PWR SWITCH
USB PD CHARGING PORT
LCD DRIVER POWER CON
3.3V 1A REGULATOR
CAPACITORS ON TRACE STUBS TO REDUCE EMI RADIATION
5.1V 6A REGULATOR
BATTERY BALANCING
BMS
FAN CON
PD NEGOTIATOR
BACKLIGHT CON
BATTERY CHARGER
OR'ING POWER SELECTION
Place NTC between batteries Stops charging when temp below 0°C or above 69°C
Charge current I=200mV/R =200mV/68mΩ =2.94A
